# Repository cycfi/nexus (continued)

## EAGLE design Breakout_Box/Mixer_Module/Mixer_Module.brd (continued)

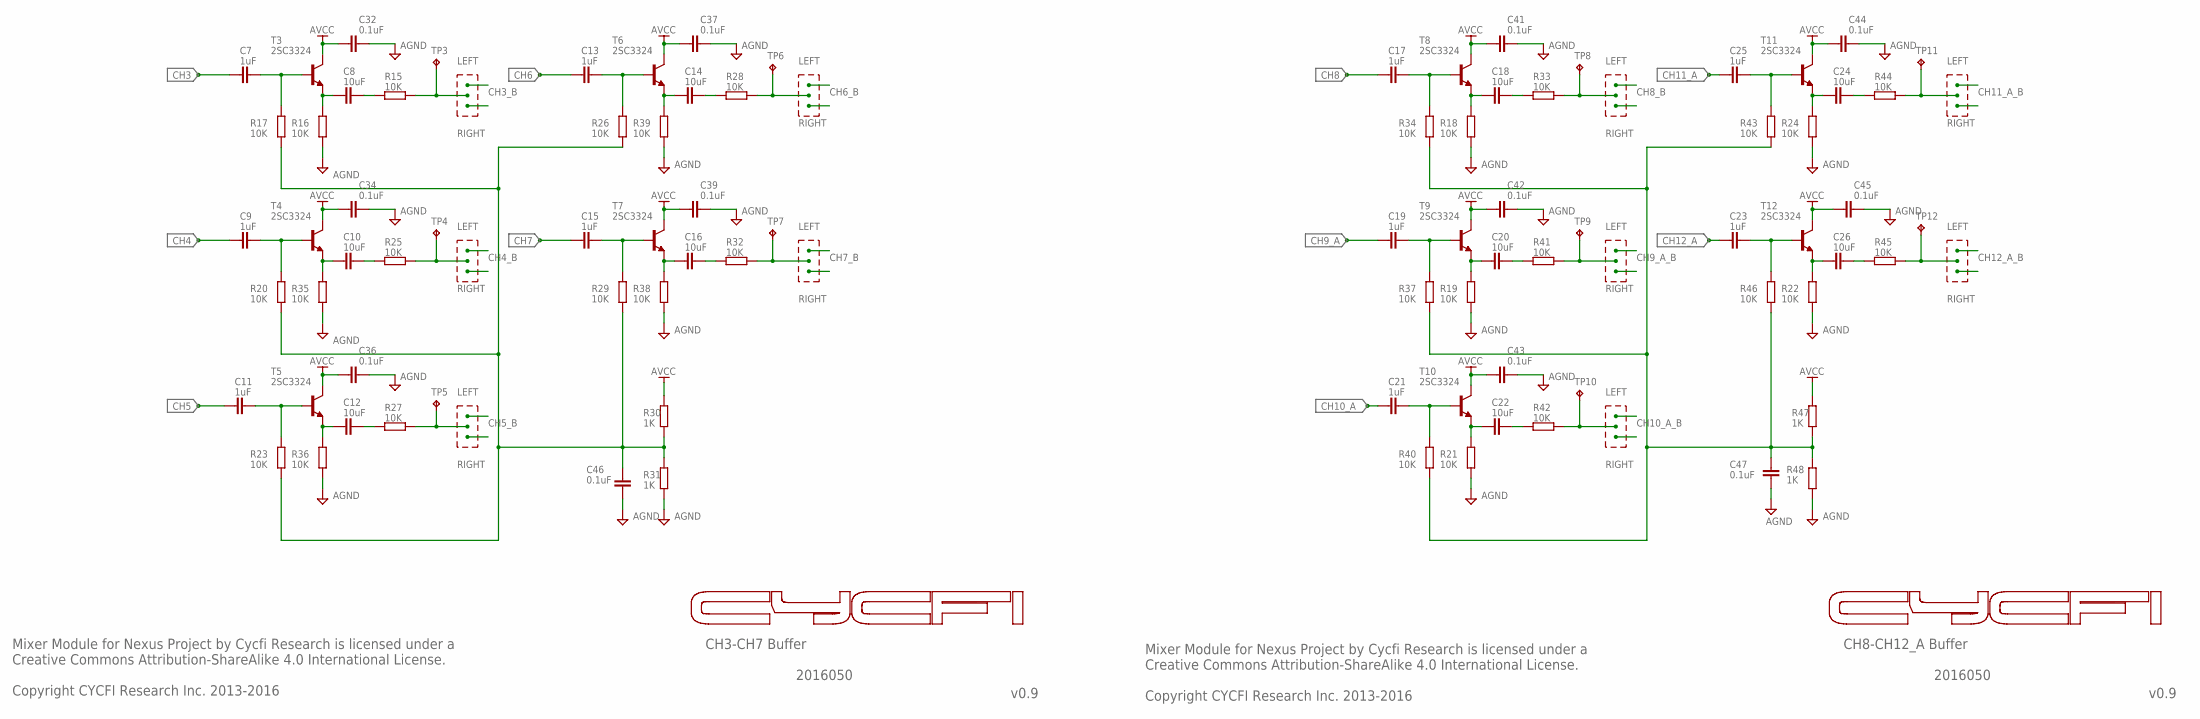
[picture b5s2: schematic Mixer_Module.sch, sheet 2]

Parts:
C7, C9, C11, C13, C15, C17, C19, C21, C23, C25: 1uF; C0603
C8, C10, C12, C14, C16, C18, C20, C22, C24, C26: 10uF; C0603
C32, C34, C36, C37, C39, C41, C42, C43, C44, C45, C46, C47: 0.1uF; C0603
R15, R16, R17, R18, R19, R20, R21, R22, R23, R24, R25, R26, R27, R28, R29, R32, R33, R34, R35, R36, R37, R38, R39, R40, R41, R42, R43, R44, R45, R46: 10K; R0402
R30, R31, R47, R48: 1K; R0402
T3, T4, T5, T6, T7, T8, T9, T10, T11, T12: 2SC3324; SOT23
TP3, TP4, TP5, TP6, TP7, TP8, TP9, TP10, TP11, TP12: TPB1,27; B1,27

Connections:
AGND: C32.1, C34.1, C36.1, C37.1, C39.1, C41.1, C42.1, C43.1, C44.1, C45.1, C46.1, C47.1, R16.2, R18.2, R19.2, R21.2, R22.2, R24.2, R31.1, R35.2, R36.2, R38.2, R39.2, R48.1; also elsewhere on the board
AVCC: C32.2, C34.2, C36.2, C37.2, C39.2, C41.2, C42.2, C43.2, C44.2, C45.2, R30.2, R47.2, T3.3 (C), T4.3 (C), T5.3 (C), T6.3 (C), T7.3 (C), T8.3 (C), T9.3 (C), T10.3 (C), T11.3 (C), T12.3 (C); also elsewhere on the board
CH3: C7.1; also elsewhere on the board
CH3_B: R15.2, TP3.TP; also elsewhere on the board
CH4: C9.1; also elsewhere on the board
CH4_B: R25.2, TP4.TP; also elsewhere on the board
CH5: C11.1; also elsewhere on the board
CH5_B: R27.2, TP5.TP; also elsewhere on the board
CH6: C13.1; also elsewhere on the board
CH6_B: R28.2, TP6.TP; also elsewhere on the board
CH7: C15.1; also elsewhere on the board
CH7_B: R32.2, TP7.TP; also elsewhere on the board
CH8: C17.1; also elsewhere on the board
CH8_B: R33.2, TP8.TP; also elsewhere on the board
CH9_A: C19.1; also elsewhere on the board
CH9_A_B: R41.2, TP9.TP; also elsewhere on the board
CH10_A: C21.1; also elsewhere on the board
CH10_A_B: R42.2, TP10.TP; also elsewhere on the board
CH11_A: C25.1; also elsewhere on the board
CH11_A_B: R44.2, TP11.TP; also elsewhere on the board
CH12_A: C23.1; also elsewhere on the board
CH12_A_B: R45.2, TP12.TP; also elsewhere on the board
unnamed: C18.1, R18.1, T8.2 (E)
unnamed: C18.2, R33.1
unnamed: C8.1, R16.1, T3.2 (E)
unnamed: C8.2, R15.1
unnamed: C7.2, R17.1, T3.1 (B)
unnamed: C10.1, R35.1, T4.2 (E)
unnamed: C10.2, R25.1
unnamed: C9.2, R20.1, T4.1 (B)
unnamed: C12.1, R36.1, T5.2 (E)
unnamed: C12.2, R27.1
unnamed: C11.2, R23.1, T5.1 (B)
unnamed: C14.1, R39.1, T6.2 (E)
unnamed: C14.2, R28.1
unnamed: C13.2, R26.1, T6.1 (B)
unnamed: C16.1, R38.1, T7.2 (E)
unnamed: C16.2, R32.1
unnamed: C15.2, R29.1, T7.1 (B)
unnamed: C46.2, R17.2, R20.2, R23.2, R26.2, R29.2, R30.1, R31.2
unnamed: C17.2, R34.1, T8.1 (B)
unnamed: C20.1, R19.1, T9.2 (E)
unnamed: C20.2, R41.1
unnamed: C19.2, R37.1, T9.1 (B)
unnamed: C22.1, R21.1, T10.2 (E)
unnamed: C22.2, R42.1
unnamed: C21.2, R40.1, T10.1 (B)
unnamed: C24.1, R24.1, T11.2 (E)
unnamed: C24.2, R44.1
unnamed: C25.2, R43.1, T11.1 (B)
unnamed: C26.1, R22.1, T12.2 (E)
unnamed: C26.2, R45.1
unnamed: C23.2, R46.1, T12.1 (B)
unnamed: C47.2, R34.2, R37.2, R40.2, R43.2, R46.2, R47.1, R48.2

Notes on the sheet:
CH3-CH7 Buffer
v0.9
2016050
CH8-CH12_A Buffer
Mixer Module for Nexus Project by Cycfi Research is licensed under a Creative Commons Attribution-ShareAlike 4.0 International License. Copyright CYCFI Research Inc. 2013-2016

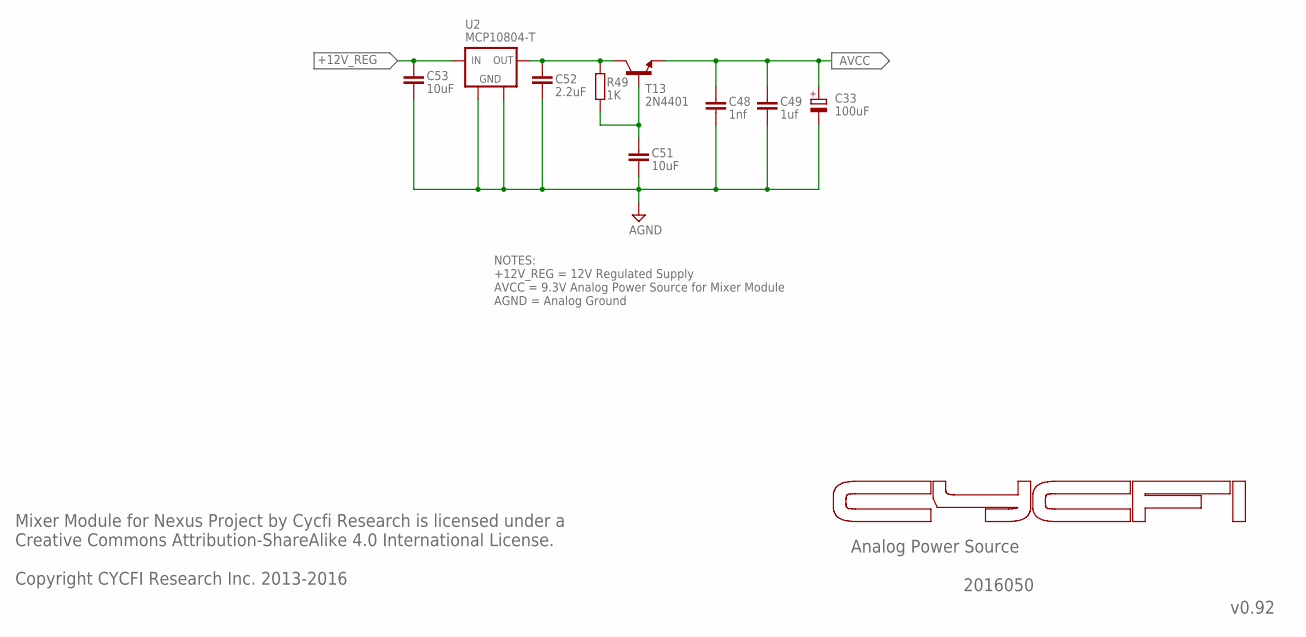
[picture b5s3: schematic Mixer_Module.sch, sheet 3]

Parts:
C33: 100uF; 153CLV-0505
C48: 1nf; C0603
C49: 1uf; C0603
C51, C53: 10uF; C0805
C52: 2.2uF; C0805
R49: 1K; R0402
T13: 2N4401; SOT23-3
U2: MCP10804-T; SOT89

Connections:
+12V_REG: C53.1, U2.3 (OUT); also elsewhere on the board
AGND: C33.-, C48.2, C49.2, C51.2, C52.2, C53.2, U2.2 (GND), U2.2@1 (GND1); also elsewhere on the board
AVCC: C33.+, C48.1, C49.1, T13.2 (E); also elsewhere on the board
unnamed: C51.1, R49.2, T13.1 (B)
unnamed: C52.1, R49.1, T13.3 (C), U2.1 (IN)

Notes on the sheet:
Analog Power Source
NOTES: +12V_REG = 12V Regulated Supply AVCC = 9.3V Analog Power Source for Mixer Module AGND = Analog Ground
v0.92
Mixer Module for Nexus Project by Cycfi Research is licensed under a Creative Commons Attribution-ShareAlike 4.0 International License. Copyright CYCFI Research Inc. 2013-2016
2016050

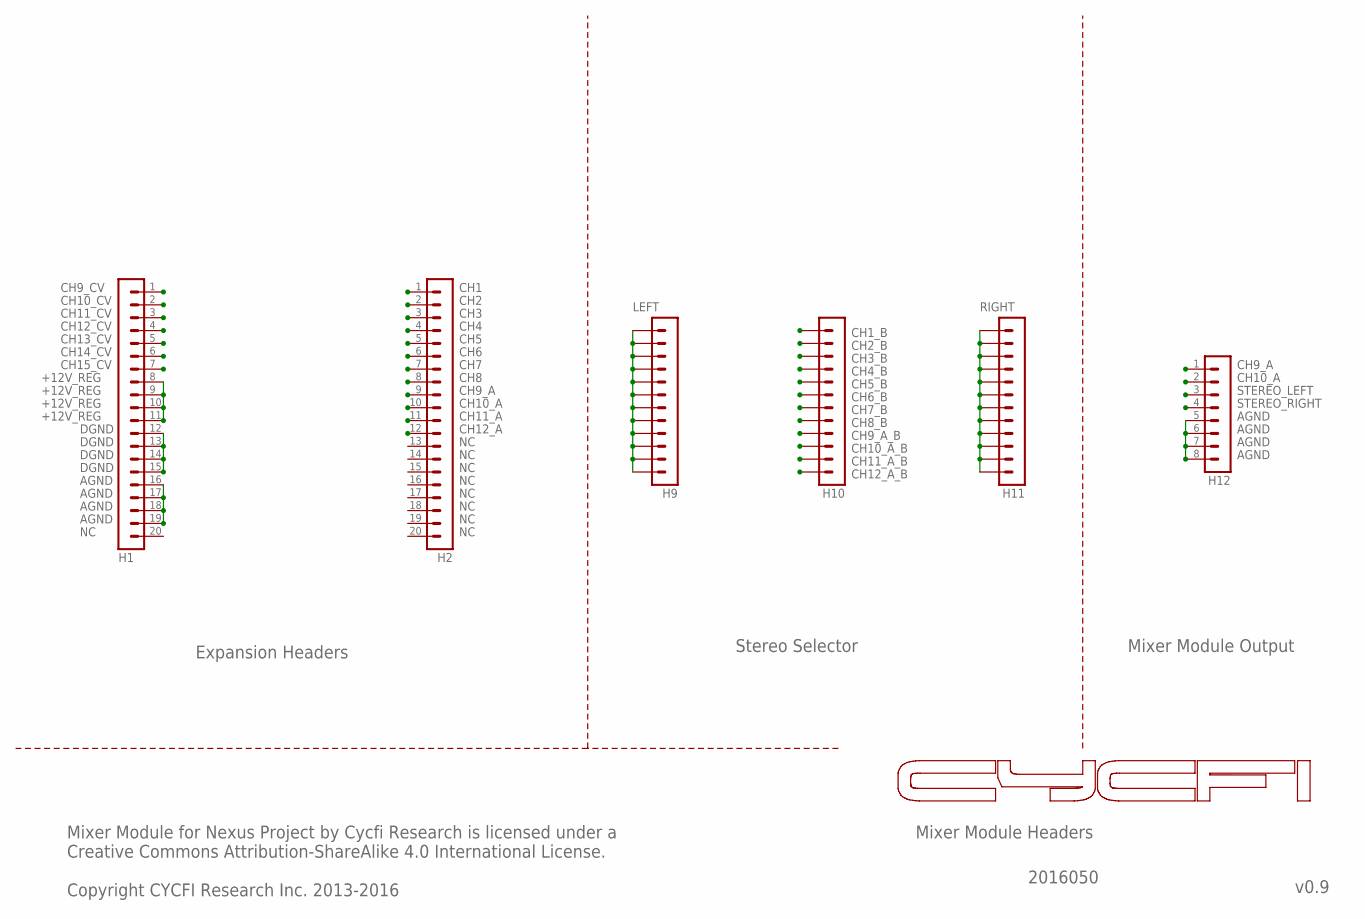
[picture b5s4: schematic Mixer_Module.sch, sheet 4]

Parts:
H1, H2: MA20-1
H9, H10, H11: 12PIN-TH-2.54MM; 12P
H12: MA08-1

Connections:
+12V_REG: H1.8, H1.9, H1.10, H1.11; also elsewhere on the board
AGND: H1.16, H1.17, H1.18, H1.19, H12.5, H12.6, H12.7, H12.8; also elsewhere on the board
CH1: H2.1; also elsewhere on the board
CH1_B: H10.1; also elsewhere on the board
CH2: H2.2; also elsewhere on the board
CH2_B: H10.2; also elsewhere on the board
CH3: H2.3; also elsewhere on the board
CH3_B: H10.3; also elsewhere on the board
CH4: H2.4; also elsewhere on the board
CH4_B: H10.4; also elsewhere on the board
CH5: H2.5; also elsewhere on the board
CH5_B: H10.5; also elsewhere on the board
CH6: H2.6; also elsewhere on the board
CH6_B: H10.6; also elsewhere on the board
CH7: H2.7; also elsewhere on the board
CH7_B: H10.7; also elsewhere on the board
CH8: H2.8; also elsewhere on the board
CH8_B: H10.8; also elsewhere on the board
CH9_A: H2.9, H12.1; also elsewhere on the board
CH9_A_B: H10.9; also elsewhere on the board
CH10_A: H2.10, H12.2; also elsewhere on the board
CH10_A_B: H10.10; also elsewhere on the board
CH11_A: H2.11; also elsewhere on the board
CH11_A_B: H10.11; also elsewhere on the board
CH12_A: H2.12; also elsewhere on the board
CH12_A_B: H10.12; also elsewhere on the board
CH15_CV: H1.7
DGND: H1.12, H1.13, H1.14, H1.15
LEFT: H9.1, H9.2, H9.3, H9.4, H9.5, H9.6, H9.7, H9.8, H9.9, H9.10, H9.11, H9.12; also elsewhere on the board
RIGHT: H11.1, H11.2, H11.3, H11.4, H11.5, H11.6, H11.7, H11.8, H11.9, H11.10, H11.11, H11.12; also elsewhere on the board
STEREO_LEFT: H12.3; also elsewhere on the board
STEREO_RIGHT: H12.4; also elsewhere on the board

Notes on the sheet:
Expansion Headers
v0.9
2016050
CH9_CV
CH10_CV
CH11_CV
CH12_CV
CH13_CV
CH14_CV
Stereo Selector
Mixer Module for Nexus Project by Cycfi Research is licensed under a Creative Commons Attribution-ShareAlike 4.0 International License. Copyright CYCFI Research Inc. 2013-2016
Mixer Module Output
Mixer Module Headers

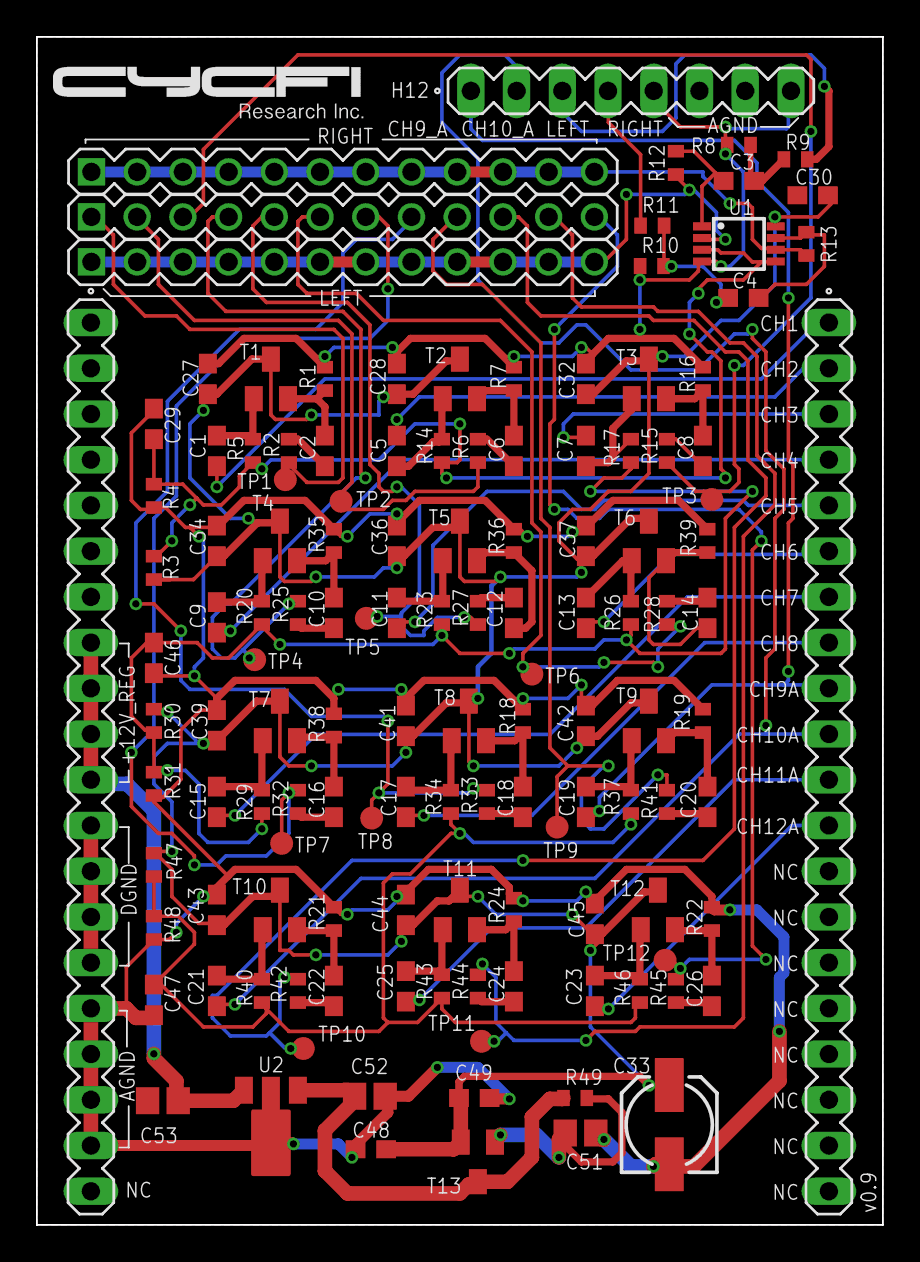
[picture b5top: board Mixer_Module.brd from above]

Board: 2 copper layers, 47.0 x 66.0 mm, 130 parts (0 on the bottom side), 77 nets.
